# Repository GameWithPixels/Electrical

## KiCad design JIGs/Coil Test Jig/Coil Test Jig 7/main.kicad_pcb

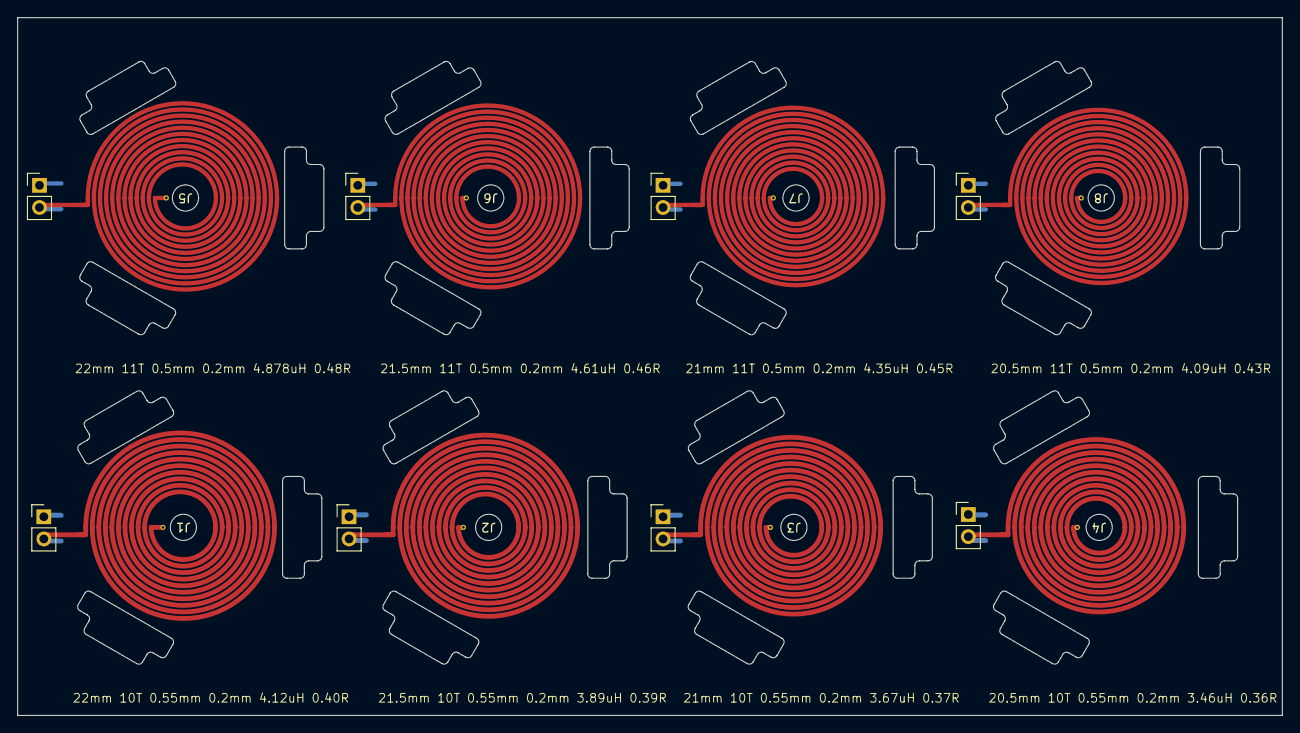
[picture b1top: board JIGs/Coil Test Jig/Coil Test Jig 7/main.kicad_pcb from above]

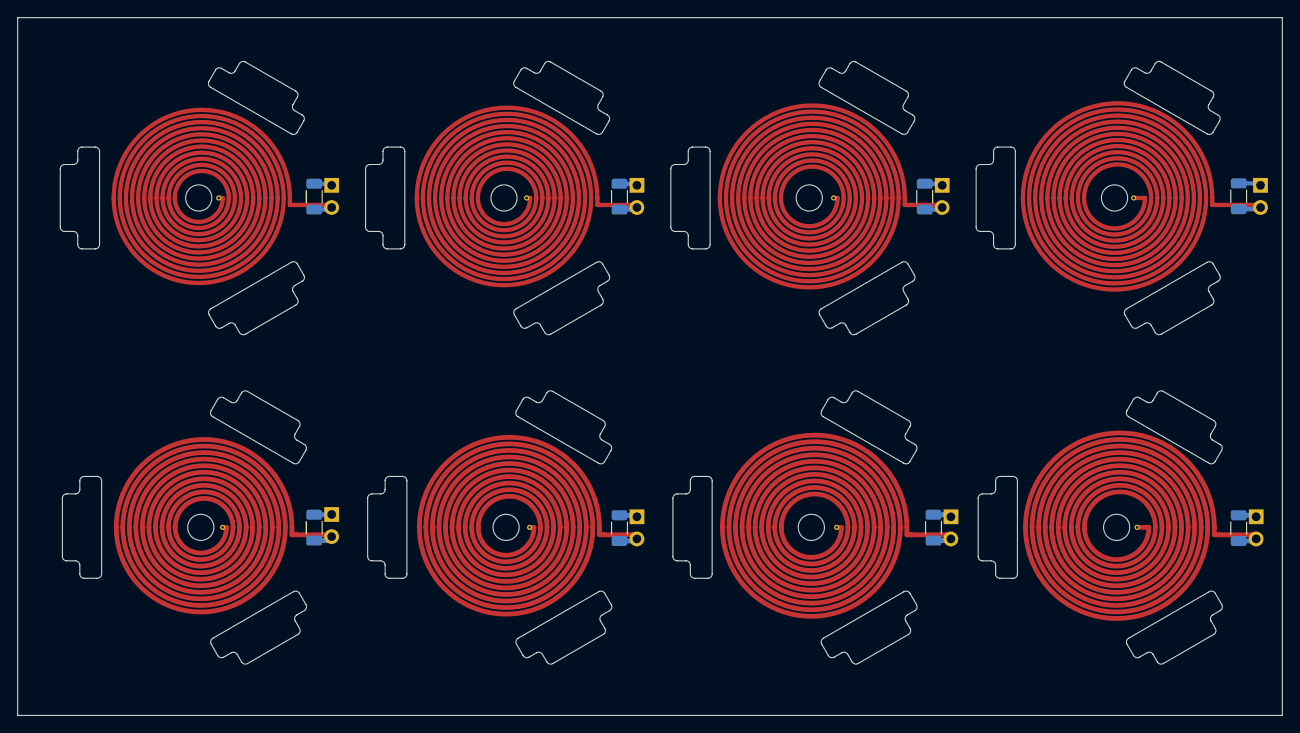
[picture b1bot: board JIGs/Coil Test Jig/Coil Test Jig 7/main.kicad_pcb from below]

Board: 4 copper layers, 145.0 x 80.0 mm, 24 parts (8 on the bottom side), 16 nets.

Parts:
C1, C2, C3, C4, C5, C6, C7, C8: 33nF 50V COG; C_1206_3216Metric
J1, J2, J3, J4, J5, J6, J7, J8: Conn_01x02_Socket; COIL_GENERATOR
J9, J10, J11, J12, J13, J14, J15, J16: Conn_01x02; PinHeader_1x02_P2.54mm_Vertical

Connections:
unnamed: C1.2, J1.1, J9.2
unnamed: C1.1, J1.2, J9.1
unnamed: C2.1, J2.2, J10.1
unnamed: C2.2, J2.1, J10.2
unnamed: C3.1, J3.2, J11.1
unnamed: C3.2, J3.1, J11.2
unnamed: C4.1, J4.2, J12.1
unnamed: C4.2, J4.1, J12.2
unnamed: C5.1, J5.2, J13.1
unnamed: C5.2, J5.1, J13.2
unnamed: C6.1, J6.2, J14.1
unnamed: C6.2, J6.1, J14.2
unnamed: C7.1, J7.2, J15.1
unnamed: C7.2, J7.1, J15.2
unnamed: C8.1, J8.2, J16.1
unnamed: C8.2, J8.1, J16.2

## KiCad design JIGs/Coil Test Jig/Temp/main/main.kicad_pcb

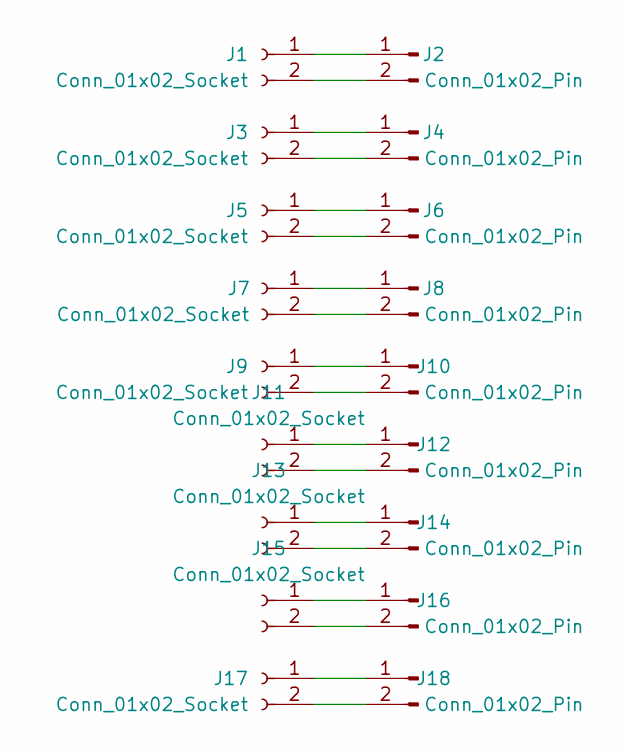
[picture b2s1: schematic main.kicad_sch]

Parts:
J1, J3, J5, J7, J9, J11, J13, J15, J17: Conn_01x02_Socket; PinHeader_1x02_P2.54mm_Vertical
J2, J4, J6, J8, J10, J12, J14, J16, J18: Conn_01x02_Pin; PinHeader_1x02_P2.54mm_Vertical

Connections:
unnamed: J1.1, J2.1
unnamed: J1.2, J2.2
unnamed: J3.1, J4.1
unnamed: J3.2, J4.2
unnamed: J5.1, J6.1
unnamed: J5.2, J6.2
unnamed: J7.1, J8.1
unnamed: J7.2, J8.2
unnamed: J9.1, J10.1
unnamed: J9.2, J10.2
unnamed: J11.1, J12.1
unnamed: J11.2, J12.2
unnamed: J13.1, J14.1
unnamed: J13.2, J14.2
unnamed: J15.1, J16.1
unnamed: J15.2, J16.2
unnamed: J17.1, J18.1
unnamed: J17.2, J18.2

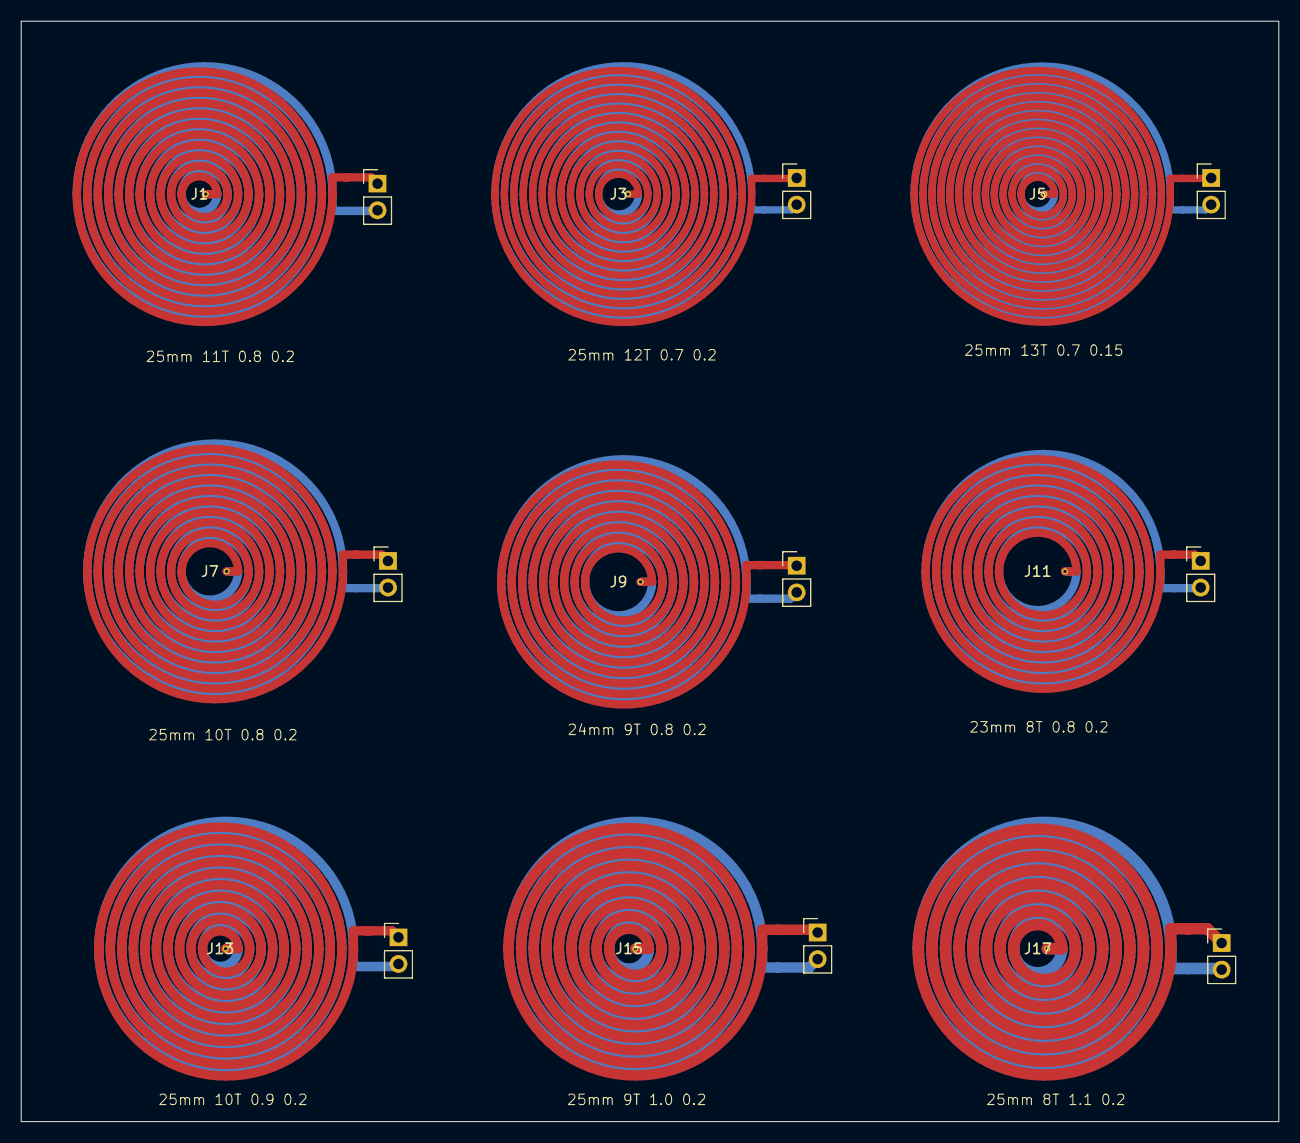
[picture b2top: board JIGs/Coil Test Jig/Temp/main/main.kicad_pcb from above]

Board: 2 copper layers, 120.0 x 105.0 mm, 18 parts (0 on the bottom side), 18 nets.

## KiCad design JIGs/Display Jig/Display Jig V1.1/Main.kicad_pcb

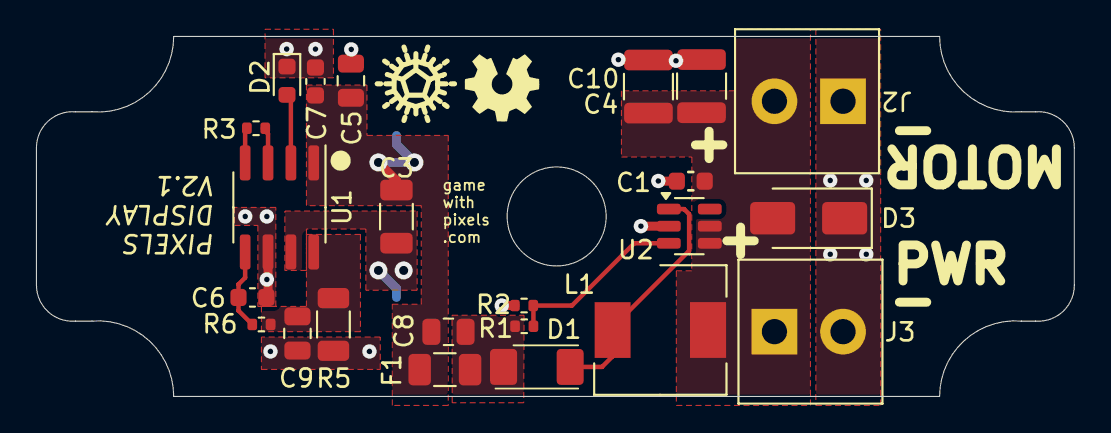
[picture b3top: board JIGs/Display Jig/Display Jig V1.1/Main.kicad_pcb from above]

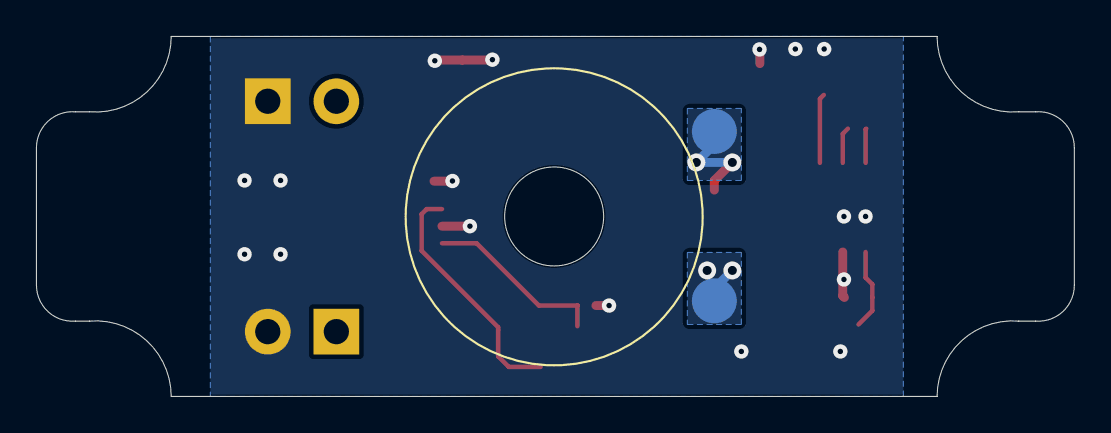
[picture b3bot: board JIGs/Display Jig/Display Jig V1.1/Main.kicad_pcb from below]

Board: 2 copper layers, 57.7 x 20.0 mm, 26 parts (3 on the bottom side), 12 nets.

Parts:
C1, C6, C7: 0.1uF 16V 10% X7R; C_0603_1608Metric
C3: 33nF 50V COG; C_1206_3216Metric
C4, C10: 22uF 25V; C_1210_3225Metric
C5: 22uF 25V 20% X5R; C_0805_2012Metric
C8, C9: 10uF 50V 10% X5R; C_0805_2012Metric
D1: D; SMAF
D2: LED; LED_0603_1608Metric
D3: D_TVS; D_SMA
F1: 250mA 150mR; Fuse_1206_3216Metric
J1: TX_Coil; TX Coil
J2, J3: Screw_Terminal_01x02; DB125-3.81-2P-GN-S
J6: Coil B; TestPoint_Pad_D2.0mm_V1.1
J9: Coil A; TestPoint_Pad_D2.0mm_V1.1
L1: 10uH 500mA; L_Wuerth_HCM-7050
R1: 470k; R_0402_1005Metric
R2: 52.3k; R_0402_1005Metric
R3: 120K 1%; R_0402_1005Metric
R5: 1.0R; R_1206_3216Metric
R6: 1k 1%; R_0402_1005Metric
U1: XKT520; SOIC-8_3.9x4.9mm_P1.27mm
U2: MT3608B; SOT-23-6

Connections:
+6V: C8.2, D1.1 (K), F1.1, R1.1
/DRIVE: C3.1, J9.1, U1.7 (OUT)
/SW: D1.2 (A), L1.2, U2.1 (SW)
GND: C1.2, C4.2, C5.2, C6.1, C7.2, C9.2, C10.2, D2.1 (K), D3.1 (A1), J2.1, J3.2, R2.2, R5.1, U1.6 (VSS), U2.2 (GND)
GNDPWR: C9.1, R5.2, R6.2, U1.8 (PVSS)
unnamed: D2.2 (A), U1.2 (LED)
unnamed: R3.1, U1.4 (R)
unnamed: R3.2, U1.3 (R)
unnamed: C6.2, R6.1, U1.5 (FB)
unnamed: R1.2, R2.1, U2.3 (FB)
VBUS: C1.1, C4.1, C10.1, D3.2 (A2), J2.2, J3.1, L1.1, U2.4 (EN), U2.5 (IN)
VCC: C3.2, C5.1, C7.1, C8.1, F1.2, J6.1, U1.1 (VDD)

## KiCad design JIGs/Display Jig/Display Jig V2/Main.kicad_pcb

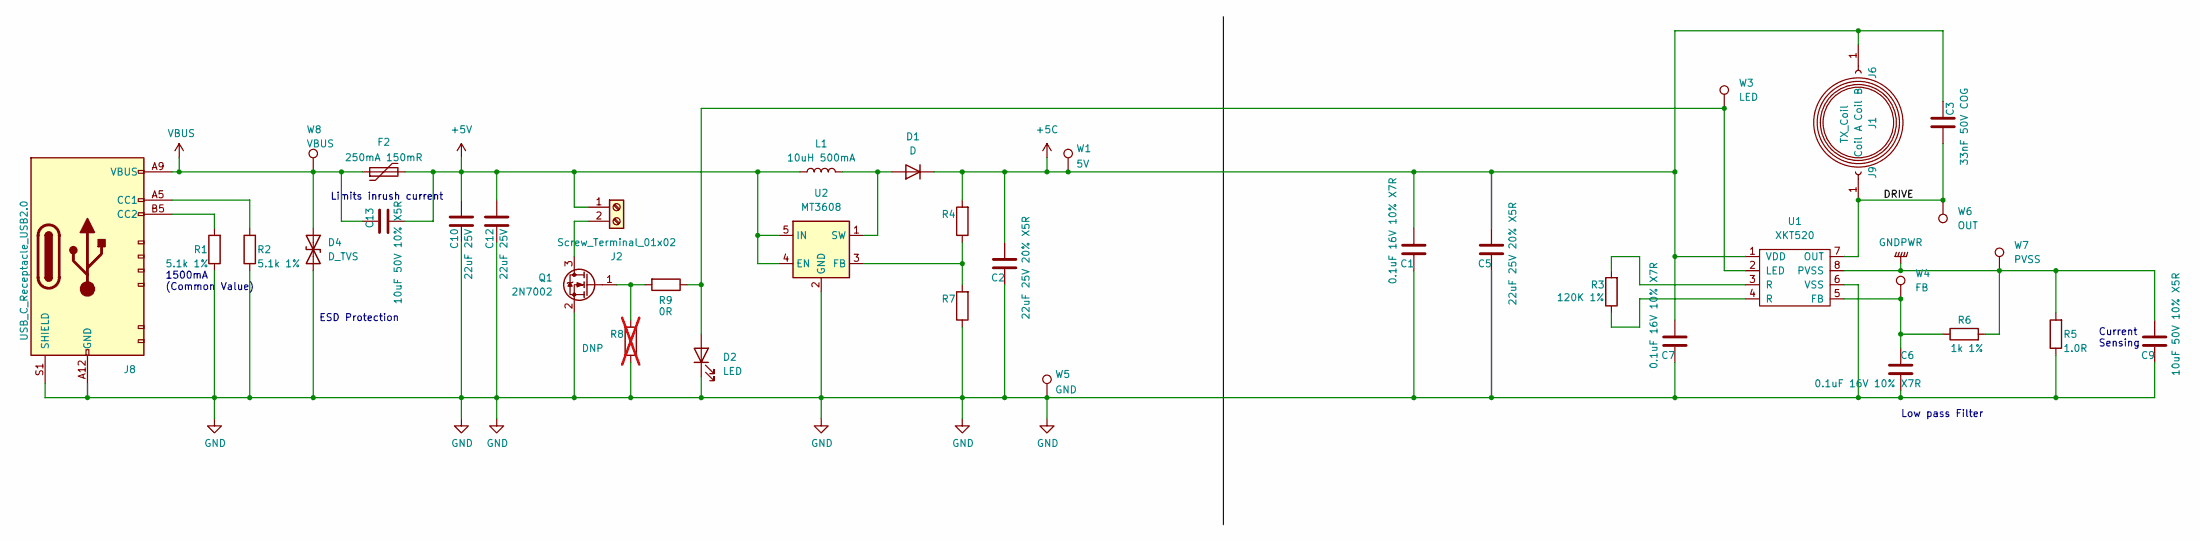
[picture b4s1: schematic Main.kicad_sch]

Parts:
C1, C6, C7: 0.1uF 16V 10% X7R; C_0603_1608Metric; Part Number CL10B104KO8NNNC; LCSC Part Number C66501
C2, C5: 22uF 25V 20% X5R; C_0805_2012Metric; Part Number GRM21BR61E226ME44L; LCSC Part Number C86816
C3: 33nF 50V COG; C_1206_3216Metric; Part Number GRM3195C1H333JA01J
C9: 10uF 50V 10% X5R; C_0805_2012Metric; Part Number GRM21BR61H106KE43L
C10, C12: 22uF 25V; C_1210_3225Metric; Manufacturer Part Number CL31A226KAHNNNE; LCSC Part Number C12891
C13: 10uF 50V 10% X5R; C_0805_2012Metric; Part Number GRM21BR61H106KE43L; LCSC Part Number C440198
D1: D; Nexperia_CFP3_SOD-123W
D2: LED; LED_0603_1608Metric; Part Number LTST-C191KRKT; LCSC Part Number C125099
D4: D_TVS; DFN; Part Number LXES1UTAA1-157; LCSC Part Number C5210979
F2: 250mA 150mR; Fuse_1206_3216Metric; Part Number BSMD1206-025-33V; LCSC Part Number C2977524
J1: TX_Coil; TX Coil
J2: Screw_Terminal_01x02; DB125-3.81-2P-GN-S; Manufacturer Part Number DB125-3.81-2P-GN-S; LCSC Part Number C395878
J6: Coil B; COIL_CON
J8: USB_C_Receptacle_USB2.0; USB-C-SMD_10P-P1.00-L6.8-W8.9; Part Number TYPE-C-31-M-17; LCSC Part Number C283540
J9: Coil A; COIL_CON
L1: 10uH 500mA; L_Taiyo-Yuden_MD-3030
Q1: 2N7002; SOT-23
R1, R2: 5.1k 1%; R_0402_1005Metric; Part Number 0402WGF5101TCE; LCSC Part Number C25905
R3: 120K 1%; R_0402_1005Metric; Part Number 0402WGF1203TCE; LCSC Part Number C25750
R4, R7: R_0402_1005Metric
R5: 1.0R; R_1206_3216Metric
R6: 1k 1%; R_0402_1005Metric; Part Number 0402WGF1001TCE; LCSC Part Number C11702
R8: DNP; R_0402_1005Metric; not fitted
R9: 0R; R_0402_1005Metric
U1: XKT520; SOIC-8_3.9x4.9mm_P1.27mm
U2: MT3608; SOT-23-6
W1: 5V; TEST_PIN
W3: LED; TEST_PIN
W4: FB; TEST_PIN
W5: GND; TEST_PIN
W6: OUT; TEST_PIN
W7: PVSS; TEST_PIN
W8: VBUS; TEST_PIN

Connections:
+5C: C1.1, C2.1, C3.2, C5.1, C7.1, D1.1 (K), J6.1, R4.2, U1.1 (VDD), W1.1
+5V: C10.1, C12.1, C13.1, F2.2, J2.1, L1.1, U2.4 (EN), U2.5 (IN)
/DRIVE: C3.1, J9.1, U1.7 (OUT), W6.1
GND: C1.2, C2.2, C5.2, C6.1, C7.2, C9.2, C10.2, C12.2, D2.1 (K), D4.2 (A2), J8.A12 (GND), J8.B12 (GND), J8.S1 (SHIELD), Q1.2 (S), R1.1, R2.1, R5.1, R7.1, R8.1, U1.6 (VSS), U2.2 (GND), W5.1
GNDPWR: C9.1, R5.2, R6.2, U1.8 (PVSS), W7.1
unnamed: D1.2 (A), L1.2, U2.1 (SW)
unnamed: D2.2 (A), R9.1, U1.2 (LED), W3.1
unnamed: J2.2, Q1.3 (D)
unnamed: J8.A5 (CC1), R2.2
unnamed: J8.B5 (CC2), R1.2
unnamed: Q1.1 (G), R8.2, R9.2
unnamed: R3.1, U1.4 (R)
unnamed: R3.2, U1.3 (R)
unnamed: C6.2, R6.1, U1.5 (FB), W4.1
unnamed: R4.1, R7.2, U2.3 (FB)
VBUS: C13.2, D4.1 (A1), F2.1, J8.A9 (VBUS), J8.B9 (VBUS), W8.1

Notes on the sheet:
ESD Protection
Current Sensing
1500mA (Common Value)
Low pass Filter
Limits inrush current

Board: 2 copper layers, 36 parts (0 on the bottom side), 16 nets, no tracks yet.

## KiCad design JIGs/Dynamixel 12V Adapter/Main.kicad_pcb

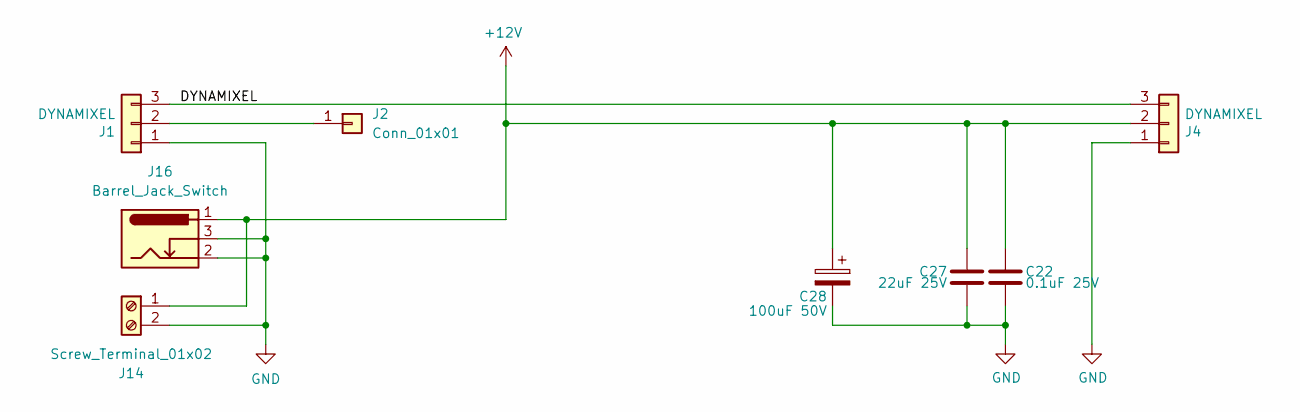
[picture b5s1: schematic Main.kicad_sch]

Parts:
C22: 0.1uF 25V; C_0402_1005Metric; Manufacturer Part Number CC0402KRX7R8BB104; LCSC Part # C105883
C27: 22uF 25V; C_1210_3225Metric; Manufacturer Part Number CL31A226KAHNNNE; LCSC Part # C12891
C28: 100uF 50V; CP_Elec_6.3x5.4; Manufacturer Part Number UWX1C101MCL1GB; LCSC Part # C97807
J1, J4: DYNAMIXEL; JST_EH_S3B-EH_1x03_P2.50mm_Horizontal; Manufacturer Part Number 22-05-7035; LCSC Part # C185225
J2: Conn_01x01; PinHeader_1x01_P2.54mm_Vertical
J14: Screw_Terminal_01x02; DB125-3.81-2P-GN-S; Manufacturer Part Number DB125-3.81-2P-GN-S; LCSC Part # C395878
J16: Barrel_Jack_Switch; BARREL_JACK; Manufacturer Part Number DC005-2.5; LCSC Part # C7507454

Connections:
+12V: C22.1, C27.1, C28.1, J4.2, J14.1, J16.1
/DYNAMIXEL: J1.3, J4.3
GND: C22.2, C27.2, C28.2, J1.1, J4.1, J14.2, J16.2, J16.3
unnamed: J1.2, J2.1

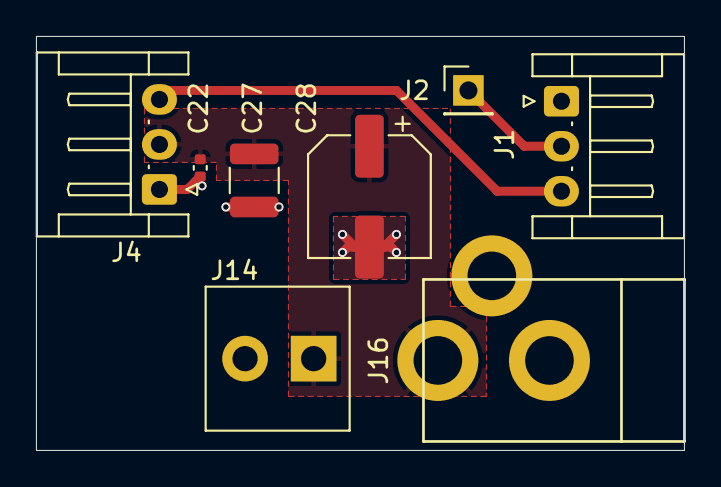
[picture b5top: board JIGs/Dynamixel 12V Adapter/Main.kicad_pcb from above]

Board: 2 copper layers, 36.0 x 23.0 mm, 8 parts (0 on the bottom side), 4 nets.

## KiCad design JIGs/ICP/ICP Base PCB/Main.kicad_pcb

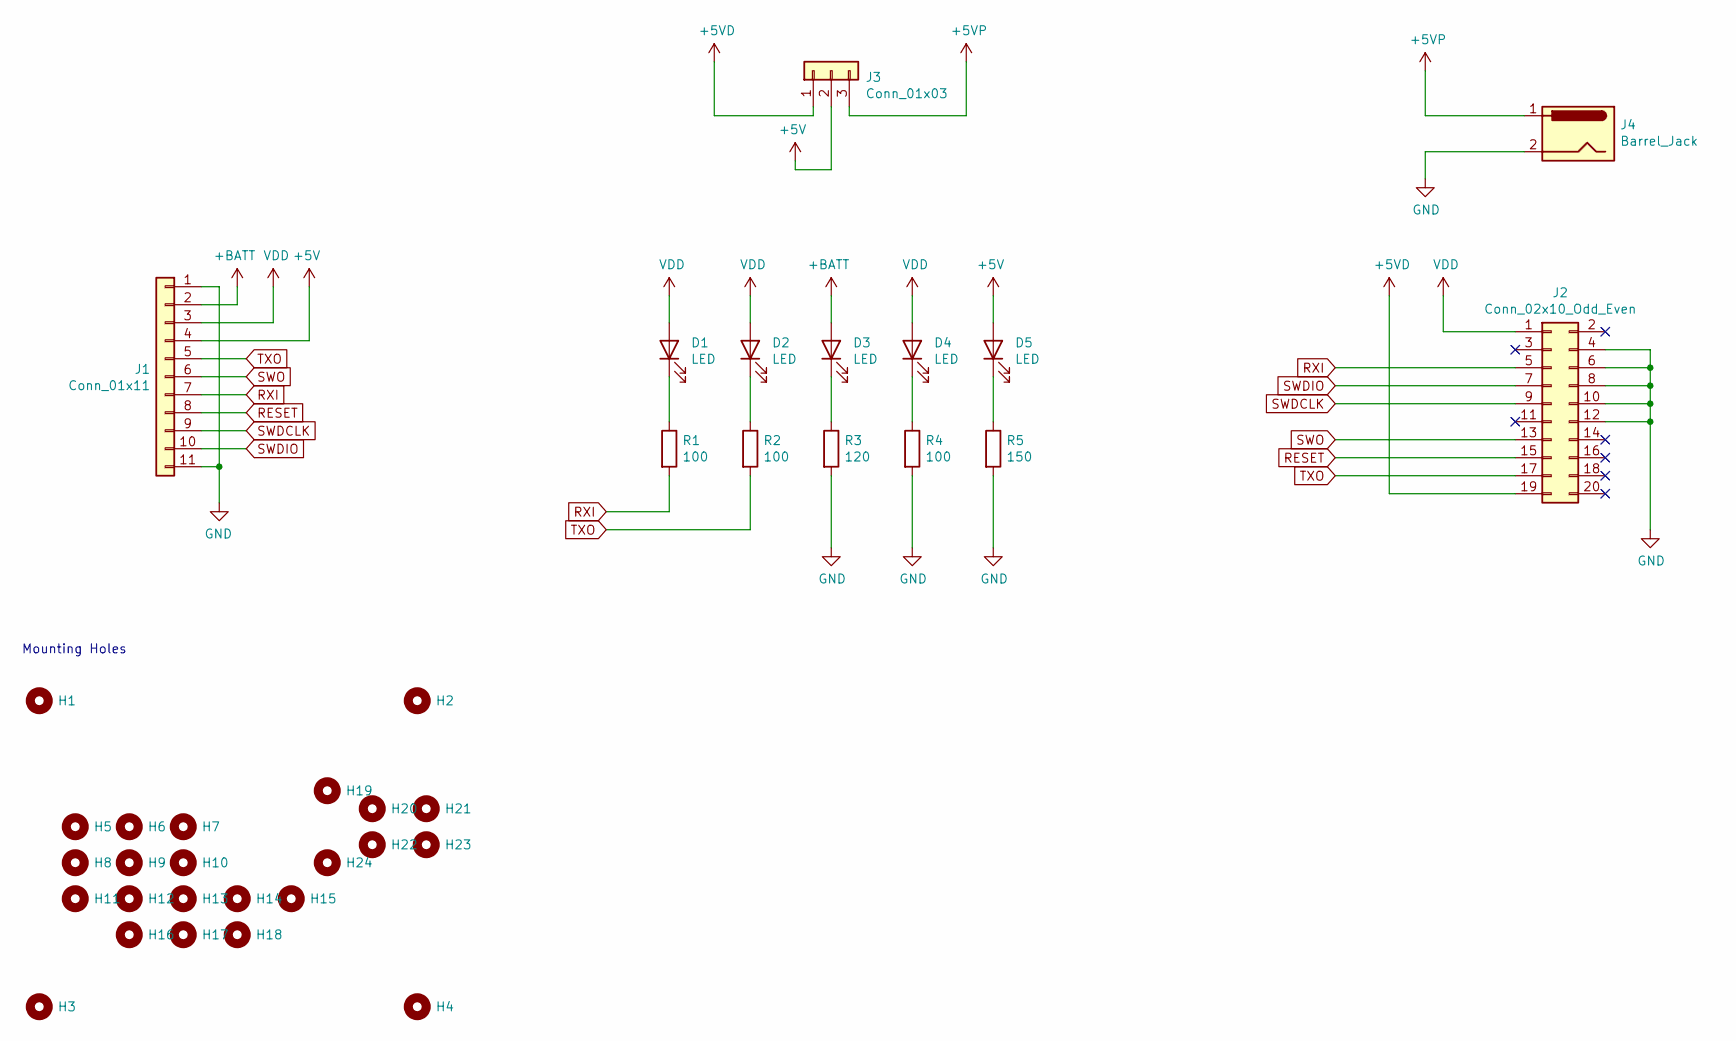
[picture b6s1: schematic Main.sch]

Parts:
D1, D2, D3, D4, D5: LED; D_0603_1608Metric; JLCPCB Part Number C72043
H1, H2, H3, H4, H20, H21, H22, H23: MountingHole; MountingHole_4.3mm_M4
H5, H6, H7, H8, H9, H10, H11, H12, H13, H14, H15, H16, H17, H18: MountingHole; MountingHole_3.2mm_M3
H19, H24: MountingHole; MountingHole_3.5mm
J1: Conn_01x11; ICP-POGO-11-BOTTOM
J2: Conn_02x10_Odd_Even; IDC-Header_2x10_P2.54mm_Vertical
J3: Conn_01x03; PinHeader_1x03_P2.54mm_Vertical
J4: Barrel_Jack; BARREL_JACK
R1, R2, R4: 100; R_0603_1608Metric; JLCPCB Part Number C22775
R3: 120; R_0603_1608Metric; JLCPCB Part Number C22775
R5: 150; R_0603_1608Metric; JLCPCB Part Number C22775

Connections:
+5V: D5.2 (A), J1.4, J3.2
+5VD: J2.19, J3.1
+5VP: J3.3, J4.1
+BATT: D3.2 (A), J1.2
GND: J1.1, J1.11, J2.4, J2.6, J2.8, J2.10, J2.12, J4.2, R3.2, R4.2, R5.2
unnamed: D1.1 (K), R1.1
unnamed: D2.1 (K), R2.1
unnamed: D3.1 (K), R3.1
unnamed: D4.1 (K), R4.1
unnamed: D5.1 (K), R5.1
RESET: J1.8, J2.15
RXI: J1.7, J2.5, R1.2
SWDCLK: J1.9, J2.9
SWDIO: J1.10, J2.7
SWO: J1.6, J2.13
TXO: J1.5, J2.17, R2.2
VDD: D1.2 (A), D2.2 (A), D4.2 (A), J1.3, J2.1

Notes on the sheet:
Mounting Holes

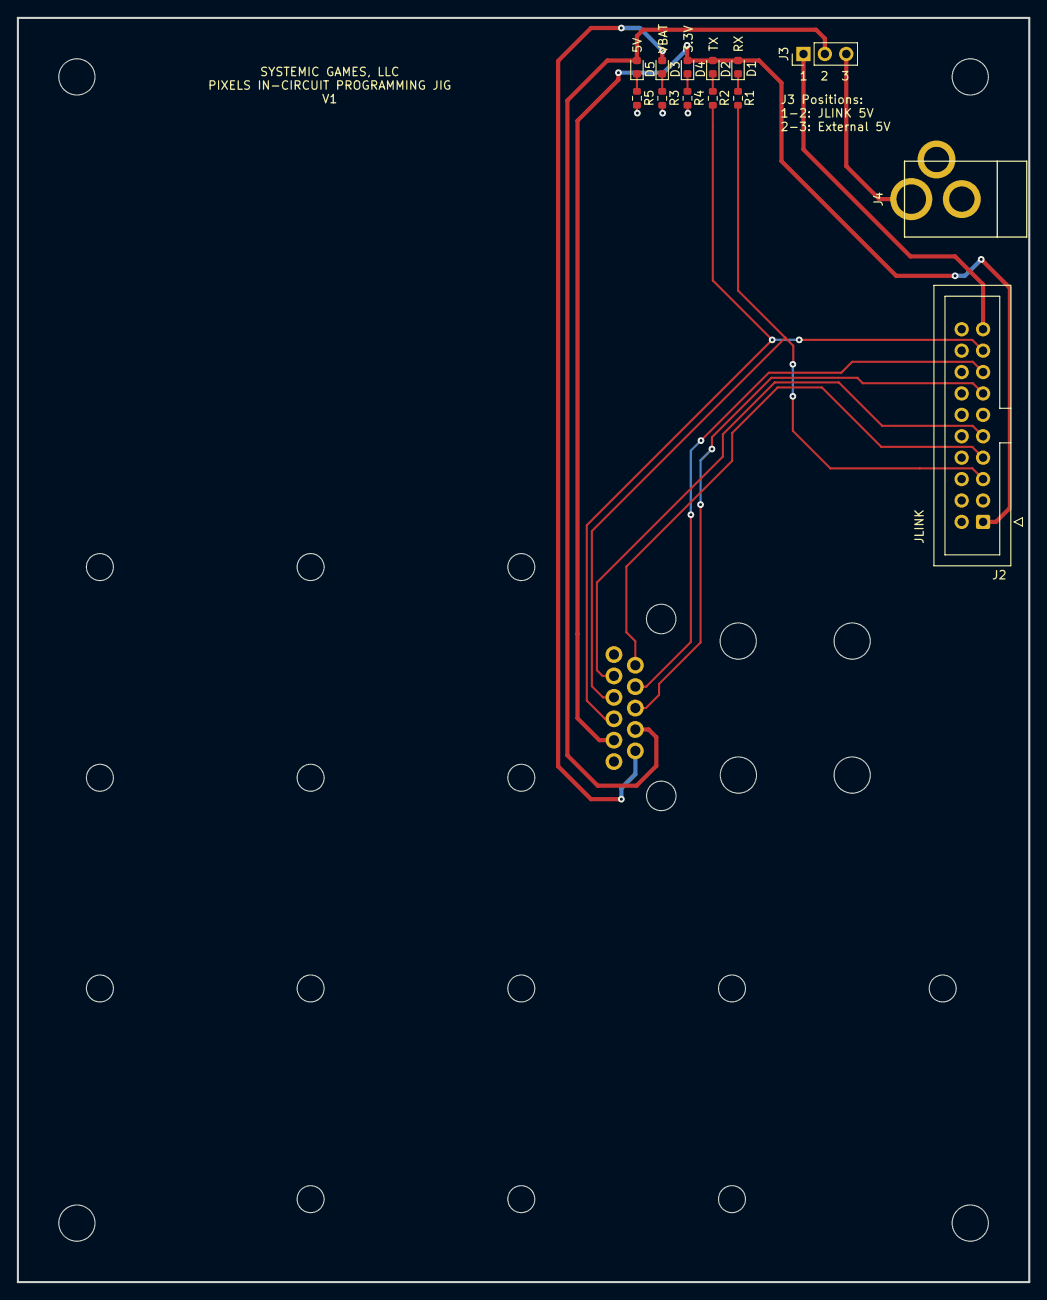
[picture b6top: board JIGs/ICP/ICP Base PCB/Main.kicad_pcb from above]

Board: 2 copper layers, 120.0 x 150.0 mm, 38 parts (1 on the bottom side), 17 nets.
